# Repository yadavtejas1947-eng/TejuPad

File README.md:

# TejuPad

TejuPad is a custom 3x3 macropad built for quick, one-handed control over the things I use most often — volume, media, function keys, and other useful shortcuts. It is powered by an RP2040 microcontroller, has a rotary encoder, an OLED display, and per-key RGB lighting, making it feel more like a compact productivity tool than a simple keyboard. 

The project started as a personal build inspired by the idea of having a small input device that sits right beside your desk and helps speed up everyday actions. Over time, it evolved into a fully designed PCB and firmware project with a complete KiCad schematic, keyboard firmware, and build notes.

## Why I built it

I wanted a small keyboard that could do the boring, repetitive things faster:

- mute and change volume
- quickly access function keys
- trigger media actions
- use RGB controls without opening software
- have a compact board that still feels fun and custom

Instead of buying a generic macro pad, I decided to design my own and learn the full process — from the PCB and enclosure ideas to firmware and configuration.

## Features

- 3x3 key matrix
- RP2040 MCU
- Rotary encoder for volume and navigation control
- 128x64 OLED display over I2C
- 9 RGB LEDs with addressable lighting
- QMK-based firmware
- Media keys and function layers
- Compact desktop-friendly layout

## Hardware overview

The board is designed around a Raspberry Pi RP2040, which is a lightweight and flexible controller for custom keyboards. The firmware setup includes:

- 3 rows x 3 columns matrix
- encoder A/B on GP2 and GP1
- OLED SCL/SDA on GP28 and GP4
- RGB data on GP26
- a standard QMK layout using `GENERIC_RP_RP2040`

## Default layout

The board uses a simple and practical layout for quick access:

### Base layer

| Key | Action |
| --- | --- |
| Top left | Mute |
| Top middle | Volume down |
| Top right | Volume up |
| Middle left | Keypad 7 |
| Middle center | Keypad 8 |
| Middle right | Keypad 9 |
| Bottom left | RGB controls |
| Bottom center | Keypad 0 |
| Bottom right | Function layer |

### Function layer

This layer gives access to common F-keys and navigation actions.

### RGB layer

This layer is used for color and brightness controls.

## Encoder behavior

The rotary encoder is mapped to useful real-world actions:

- Base layer: volume down / volume up
- Function layer: page down / page up
- RGB layer: brightness down / brightness up

## Project structure

This repository contains all the pieces needed to understand and build the project:

- `Firmware/` — QMK firmware configuration and keyboard definitions
- `Schematics/` — KiCad PCB and schematic files
- `Assests/` — supporting documents and references
- `BOM.md` — bill of materials
- `JOURNAL.md` — the build log and design progress
- `README.md` — project overview

## Firmware

The firmware is implemented in QMK and is designed to work with the custom RP2040 board.

To build the firmware from the QMK root directory:

```sh
make teju_pad:default
```

To flash it:

```sh
make teju_pad:default:flash
```

You can enter bootloader mode by:

- holding the top-left key while plugging in the keyboard
- pressing the reset button on the controller
- using the `QK_BOOT` key from the RGB layer

## Design and build notes

The project was created through a real hands-on design process:

- schematic design in KiCad
- PCB design and routing
- component footprint matching
- 3D model and enclosure exploration
- firmware mapping and layer planning
- testing and iteration

The devlog in `JOURNAL.md` documents the process in a very personal and honest way, which makes it a great companion to the technical files.

## Files to explore

- `Firmware/readme.md` — device and firmware details
- `Schematics/Schematics.kicad_sch` — electrical schematic
- `Schematics/Schematics.kicad_pcb` — PCB layout
- `JOURNAL.md` — development journal
- `BOM.md` — parts list

## License

This project is licensed under the MIT License. See `LICENSE` for details.

## Notes

This is a custom DIY keyboard project and should be treated as a personal build. It works best when paired with careful testing and hardware verification before daily use.

If you are interested in custom keyboard builds, PCB design, or QMK firmware, this project is a good example of a complete beginner-to-intermediate hardware + firmware build from scratch.

---

Built as a personal productivity keyboard project by Tejas Yadav.

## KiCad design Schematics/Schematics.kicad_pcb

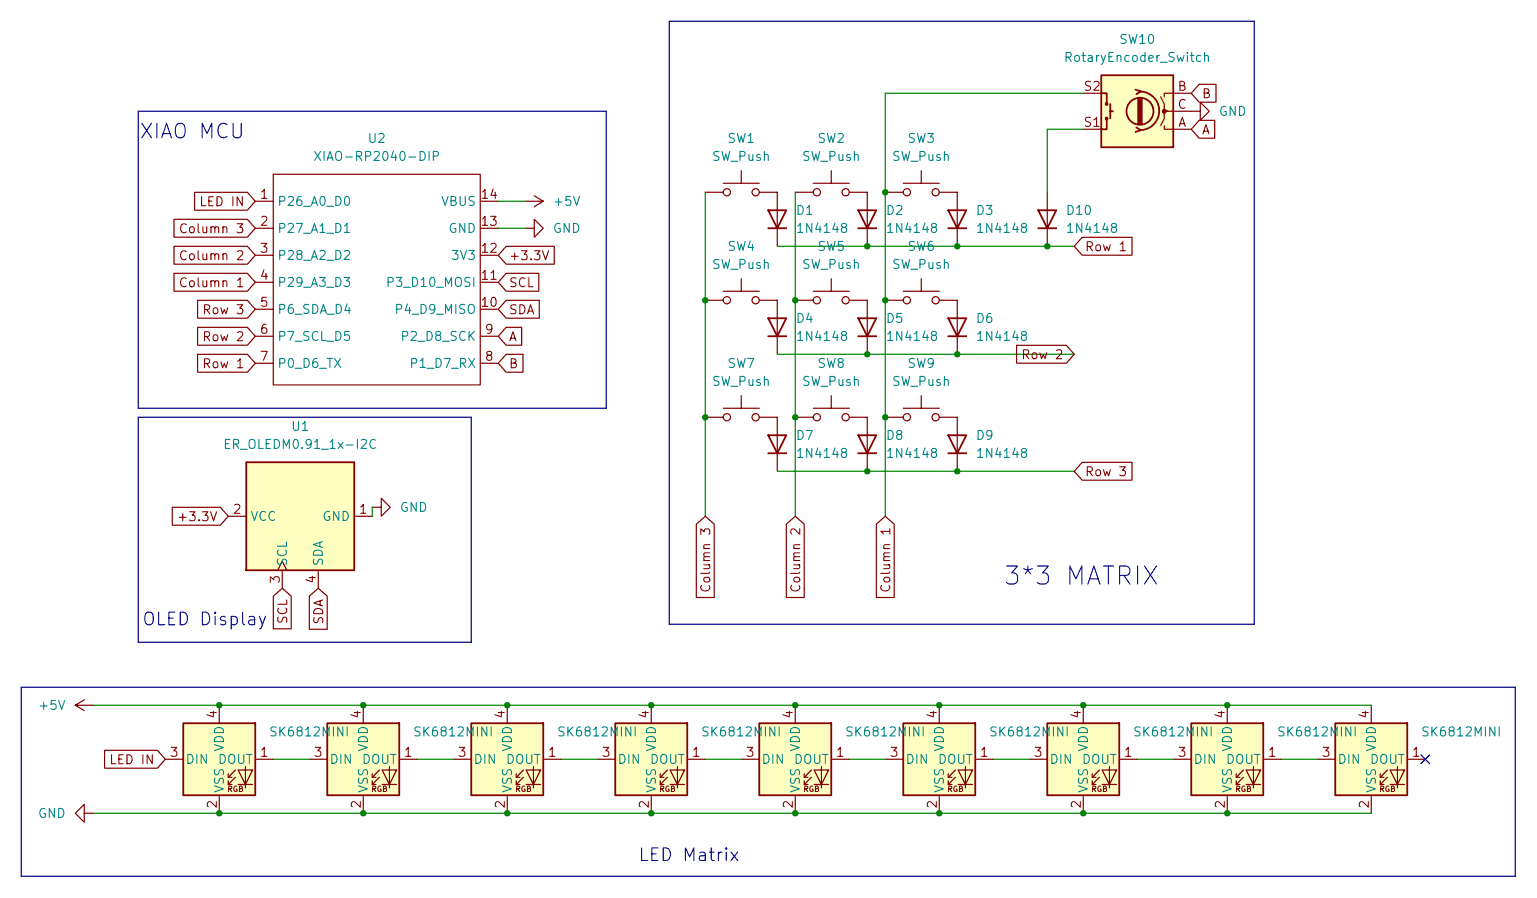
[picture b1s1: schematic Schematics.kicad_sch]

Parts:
D1, D2, D3, D4, D5, D6, D7, D8, D9, D10: 1N4148; D_DO-35_SOD27_P7.62mm_Horizontal
D11, D12, D13, D14, D15, D16, D17, D18, D19: SK6812MINI; LED_SK6812MINI_PLCC4_3.5x3.5mm_P1.75mm
SW1, SW2, SW3, SW4, SW5, SW6, SW7, SW8, SW9: SW_Push; SW_Cherry_MX_1.00u_PCB
SW10: RotaryEncoder_Switch; RotaryEncoder_Alps_EC11E-Switch_Vertical_H20mm
U1: ER_OLEDM0.91_1x-I2C
U2: XIAO-RP2040-DIP

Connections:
+3.3V: U1.2 (VCC), U2.12 (3V3)
+5V: D11.4 (VDD), D12.4 (VDD), D13.4 (VDD), D14.4 (VDD), D15.4 (VDD), D16.4 (VDD), D17.4 (VDD), D18.4 (VDD), D19.4 (VDD), U2.14 (VBUS)
A: SW10.A, U2.9 (P2_D8_SCK)
B: SW10.B, U2.8 (P1_D7_RX)
Column 1: SW3.1, SW6.1, SW9.1, SW10.S2, U2.4 (P29_A3_D3)
Column 2: SW2.1, SW5.1, SW8.1, U2.3 (P28_A2_D2)
Column 3: SW1.1, SW4.1, SW7.1, U2.2 (P27_A1_D1)
GND: D11.2 (VSS), D12.2 (VSS), D13.2 (VSS), D14.2 (VSS), D15.2 (VSS), D16.2 (VSS), D17.2 (VSS), D18.2 (VSS), D19.2 (VSS), SW10.C, U1.1 (GND), U2.13 (GND)
LED IN: D11.3 (DIN), U2.1 (P26_A0_D0)
unnamed: D1.2 (A), SW1.2
unnamed: D2.2 (A), SW2.2
unnamed: D3.2 (A), SW3.2
unnamed: D4.2 (A), SW4.2
unnamed: D5.2 (A), SW5.2
unnamed: D6.2 (A), SW6.2
unnamed: D7.2 (A), SW7.2
unnamed: D8.2 (A), SW8.2
unnamed: D9.2 (A), SW9.2
unnamed: D10.2 (A), SW10.S1
unnamed: D11.1 (DOUT), D12.3 (DIN)
unnamed: D12.1 (DOUT), D13.3 (DIN)
unnamed: D13.1 (DOUT), D14.3 (DIN)
unnamed: D14.1 (DOUT), D15.3 (DIN)
unnamed: D15.1 (DOUT), D16.3 (DIN)
unnamed: D16.1 (DOUT), D17.3 (DIN)
unnamed: D17.1 (DOUT), D18.3 (DIN)
unnamed: D18.1 (DOUT), D19.3 (DIN)
Row 1: D1.1 (K), D2.1 (K), D3.1 (K), D10.1 (K), U2.7 (P0_D6_TX)
Row 2: D4.1 (K), D5.1 (K), D6.1 (K), U2.6 (P7_SCL_D5)
Row 3: D7.1 (K), D8.1 (K), D9.1 (K), U2.5 (P6_SDA_D4)
SCL: U1.3 (SCL), U2.11 (P3_D10_MOSI)
SDA: U1.4 (SDA), U2.10 (P4_D9_MISO)

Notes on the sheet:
3*3 MATRIX
XIAO MCU
LED Matrix
OLED Display

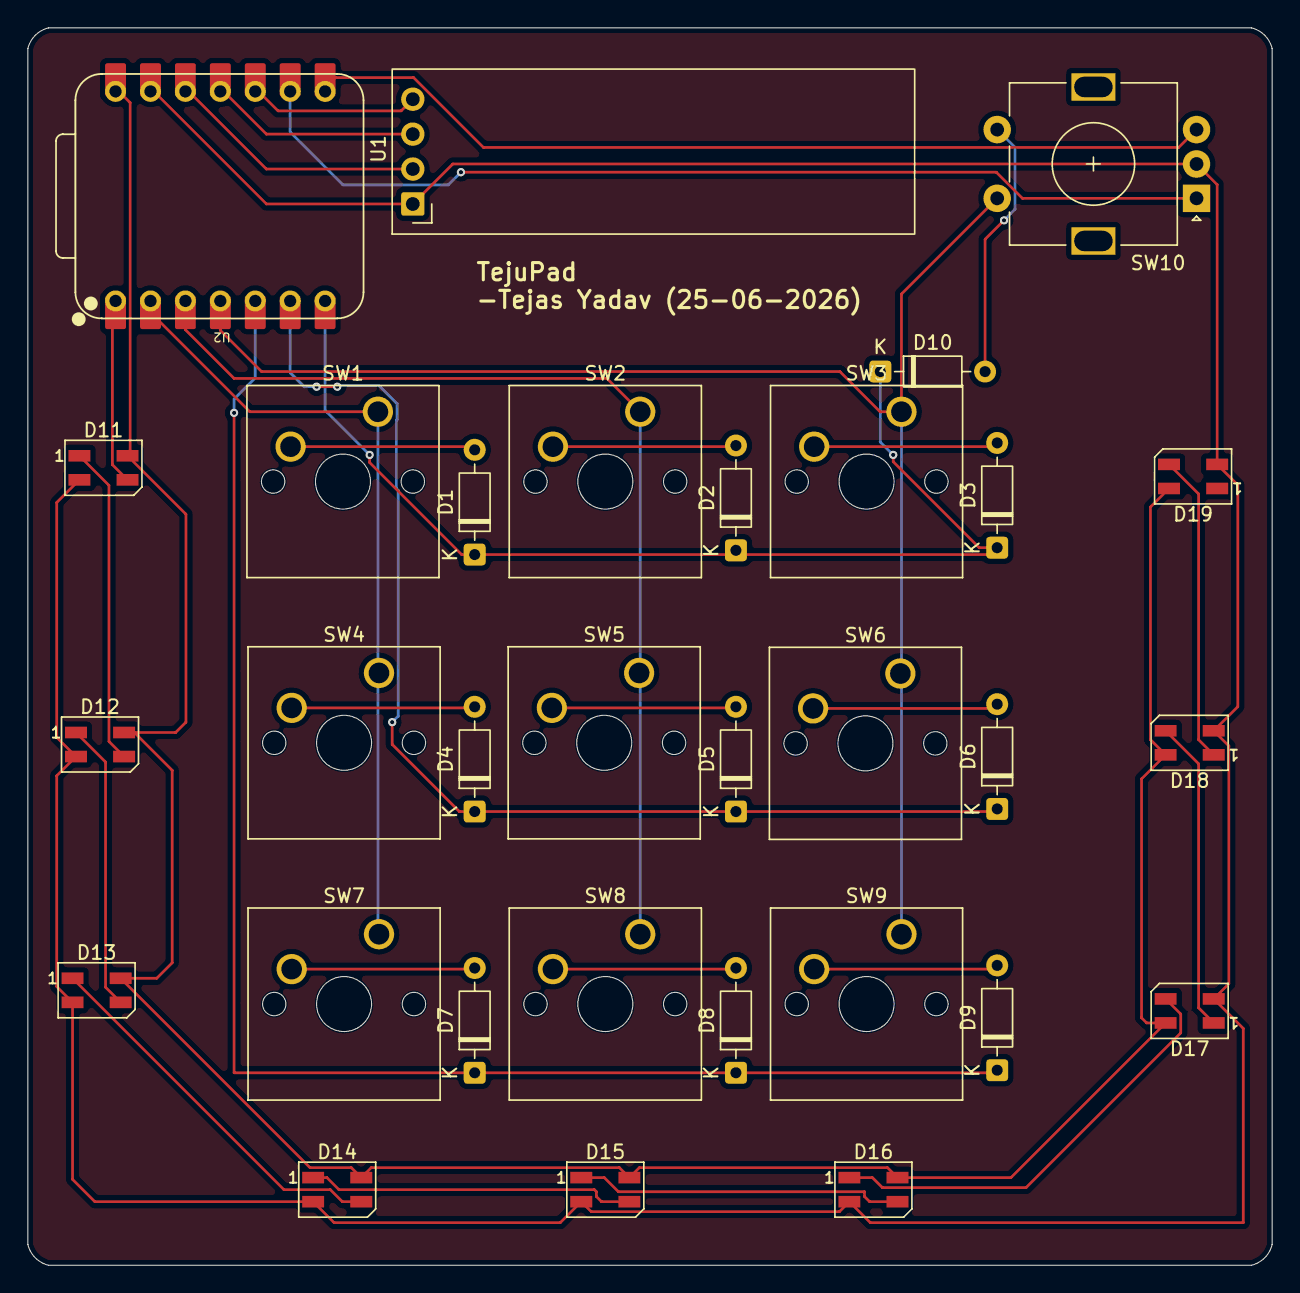
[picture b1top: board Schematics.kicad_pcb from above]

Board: 2 copper layers, 90.5 x 90.0 mm, 31 parts (0 on the bottom side), 32 nets.

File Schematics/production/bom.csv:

Designator,Footprint,Quantity,Value,LCSC Part #
"D1, D10, D2, D3, D4, D5, D6, D7, D8, D9",D_DO-35_SOD27_P7.62mm_Horizontal,10,1N4148,
"D11, D12, D13, D14, D15, D16, D17, D18, D19",LED_SK6812MINI_PLCC4_3.5x3.5mm_P1.75mm,9,SK6812MINI,
"SW1, SW2, SW3, SW4, SW5, SW6, SW7, SW8, SW9",SW_Cherry_MX_1.00u_PCB,9,SW_Push,
SW10,RotaryEncoder_Alps_EC11E-Switch_Vertical_H20mm,1,RotaryEncoder_Switch,
U1,ER_OLEDM0.91_1x-I2C,1,ER_OLEDM0.91_1x-I2C,
U2,XIAO-RP2040-DIP,1,XIAO-RP2040-DIP,

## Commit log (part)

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2026-06-25 PCB and Schematics
2026-06-25 Firmware
2026-06-25 Firmware Reshuffling
